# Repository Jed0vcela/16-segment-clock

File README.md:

# 16-segment-clock
hodiny s RPI pico a 14ti segmentovým displejem V1
Trošku se vloudila chybka při pojmenování repozitáře - displej má pouze 14segmentů...

"číslování" segmentá 14ti segmentového displeje

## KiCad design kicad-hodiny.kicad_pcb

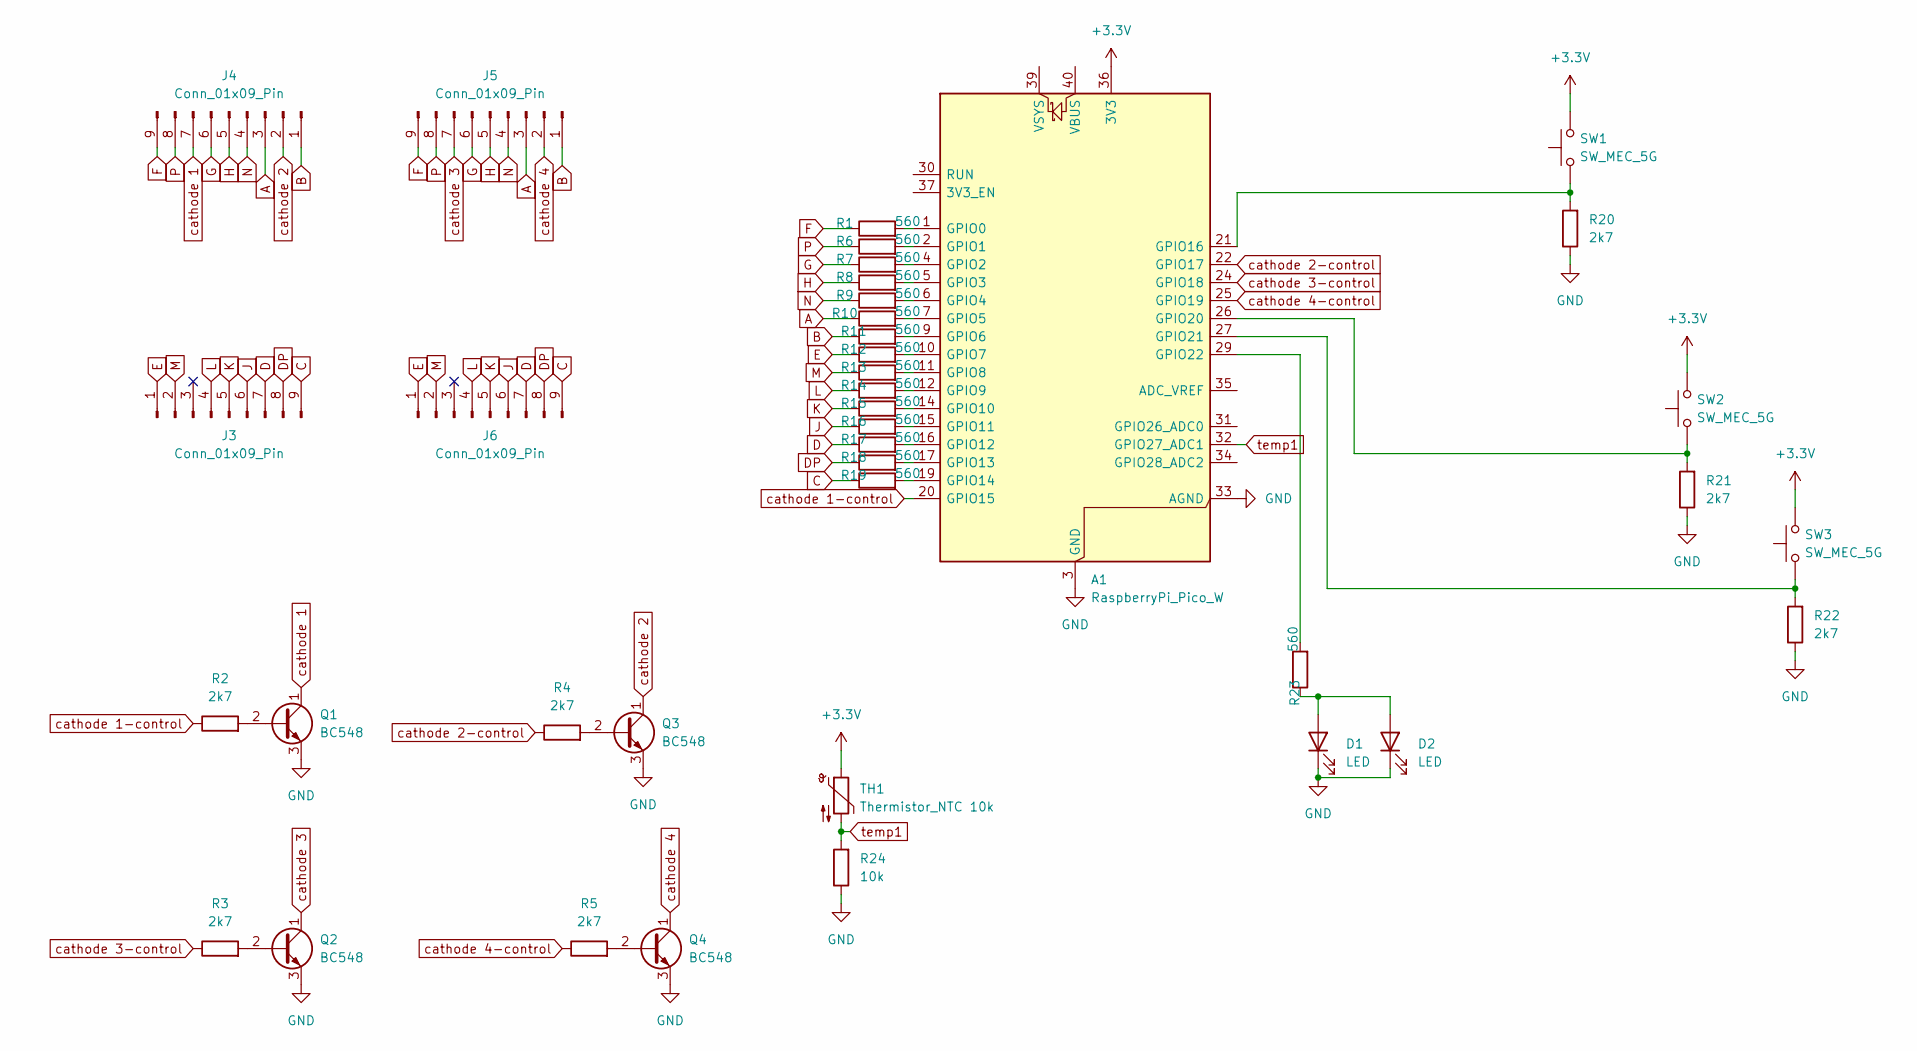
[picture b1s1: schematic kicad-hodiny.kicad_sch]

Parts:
A1: RaspberryPi_Pico_W; RaspberryPi_Pico_W_SMD_HandSolder
D1, D2: LED; LED_D3.0mm
J3, J4, J5, J6: Conn_01x09_Pin; PinSocket_1x09_P2.54mm_Vertical
Q1, Q2, Q3, Q4: BC548; TO-92L_HandSolder
R1, R6, R7, R8, R9, R10, R11, R12, R13, R14, R15, R16, R17, R18, R19, R23: 560; R_Axial_DIN0207_L6.3mm_D2.5mm_P10.16mm_Horizontal
R2, R3, R4, R5, R20, R21, R22: 2k7; R_Axial_DIN0207_L6.3mm_D2.5mm_P10.16mm_Horizontal
R24: 10k; R_Axial_DIN0207_L6.3mm_D2.5mm_P10.16mm_Horizontal
SW1, SW2, SW3: SW_MEC_5G; SW_PUSH_6mm_H4.3mm
TH1: Thermistor_NTC 10k; R_LDR_5.2x5.2mm_P3.5mm_Horizontal

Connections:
+3.3V: A1.36 (3V3), SW1.1 (A), SW2.1 (A), SW3.1 (A), TH1.1
A: J4.3, J5.3, R10.1
B: J4.1, J5.1, R11.1
C: J3.9, J6.9, R19.1
D: J3.7, J6.7, R17.1
DP: J3.8, J6.8, R18.1
E: J3.1, J6.1, R12.1
F: J4.9, J5.9, R1.1
G: J4.6, J5.6, R7.1
GND: A1.3 (GND), A1.8 (GND), A1.13 (GND), A1.18 (GND), A1.23 (GND), A1.28 (GND), A1.33 (AGND), A1.38 (GND), D1.1 (K), D2.1 (K), Q1.3 (E), Q2.3 (E), Q3.3 (E), Q4.3 (E), R20.1, R21.1, R22.1, R24.1
H: J4.5, J5.5, R8.1
J: J3.6, J6.6, R16.1
K: J3.5, J6.5, R15.1
L: J3.4, J6.4, R14.1
M: J3.2, J6.2, R13.1
N: J4.4, J5.4, R9.1
unnamed: A1.1 (GPIO0), R1.2
unnamed: A1.2 (GPIO1), R6.2
unnamed: A1.4 (GPIO2), R7.2
unnamed: A1.5 (GPIO3), R8.2
unnamed: A1.6 (GPIO4), R9.2
unnamed: A1.7 (GPIO5), R10.2
unnamed: A1.9 (GPIO6), R11.2
unnamed: A1.10 (GPIO7), R12.2
unnamed: A1.11 (GPIO8), R13.2
unnamed: A1.12 (GPIO9), R14.2
unnamed: A1.14 (GPIO10), R15.2
unnamed: A1.15 (GPIO11), R16.2
unnamed: A1.16 (GPIO12), R17.2
unnamed: A1.17 (GPIO13), R18.2
unnamed: A1.19 (GPIO14), R19.2
unnamed: A1.21 (GPIO16), R20.2, SW1.2 (A)
unnamed: A1.26 (GPIO20), R21.2, SW2.2 (A)
unnamed: A1.27 (GPIO21), R22.2, SW3.2 (A)
unnamed: A1.29 (GPIO22), R23.2
unnamed: D1.2 (A), D2.2 (A), R23.1
unnamed: Q1.2 (B), R2.2
unnamed: Q2.2 (B), R3.2
unnamed: Q3.2 (B), R4.2
unnamed: Q4.2 (B), R5.2
P: J4.8, J5.8, R6.1
cathode 1: J4.7, Q1.1 (C)
cathode 1-control: A1.20 (GPIO15), R2.1
cathode 2: J4.2, Q3.1 (C)
cathode 2-control: A1.22 (GPIO17), R4.1
cathode 3: J5.7, Q2.1 (C)
cathode 3-control: A1.24 (GPIO18), R3.1
cathode 4: J5.2, Q4.1 (C)
cathode 4-control: A1.25 (GPIO19), R5.1
temp1: A1.32 (GPIO27_ADC1), R24.2, TH1.2

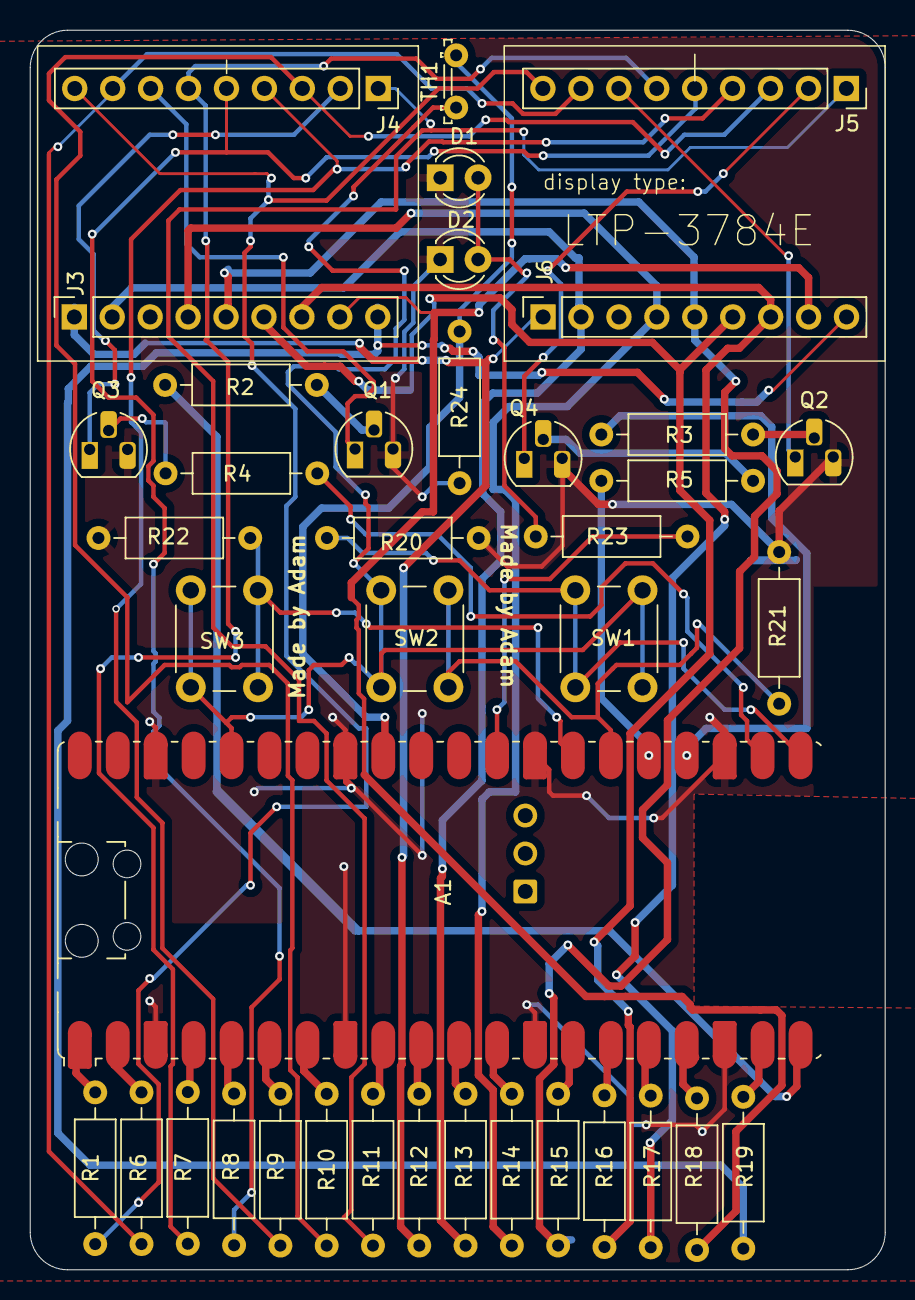
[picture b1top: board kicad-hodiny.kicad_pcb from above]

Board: 2 copper layers, 57.2 x 83.0 mm, 39 parts (0 on the bottom side), 50 nets.

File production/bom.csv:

Designator,Footprint,Quantity,Value,LCSC Part #
A1,RaspberryPi_Pico_W_SMD_HandSolder,1,RaspberryPi_Pico_W,
"D1, D2",LED_D3.0mm,2,LED,
"J3, J4, J5, J6",PinSocket_1x09_P2.54mm_Vertical,4,Conn_01x09_Pin,
"Q1, Q2, Q3, Q4",TO-92L_HandSolder,4,BC548,
"R1, R10, R11, R12, R13, R14, R15, R16, R17, R18, R19, R23, R6, R7, R8, R9",R_Axial_DIN0207_L6.3mm_D2.5mm_P10.16mm_Horizontal,16,560,
"R2, R20, R21, R22, R3, R4, R5",R_Axial_DIN0207_L6.3mm_D2.5mm_P10.16mm_Horizontal,7,2k7,
R24,R_Axial_DIN0207_L6.3mm_D2.5mm_P10.16mm_Horizontal,1,10k,
"SW1, SW2, SW3",SW_PUSH_6mm_H4.3mm,3,SW_MEC_5G,
TH1,R_LDR_5.2x5.2mm_P3.5mm_Horizontal,1,Thermistor_NTC 10k,

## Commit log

2025-05-12 upload
2025-06-04 upload testu1
2025-06-04 update segment naming
2025-06-05 chyba inicializace RTC
